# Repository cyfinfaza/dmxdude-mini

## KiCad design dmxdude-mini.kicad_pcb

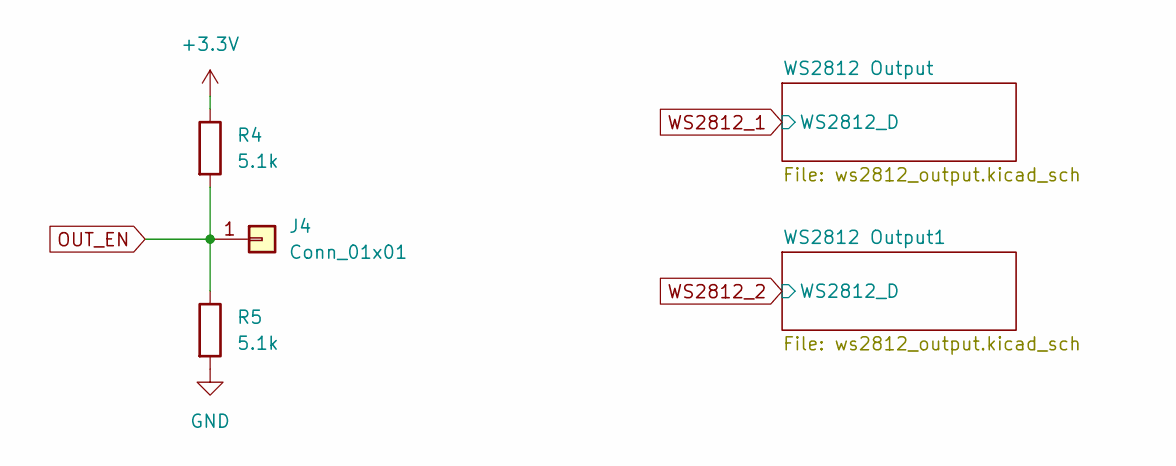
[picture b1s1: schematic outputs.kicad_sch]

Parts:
J4: Conn_01x01; PinHeader_1x01_P2.54mm_Vertical
R4, R5: 5.1k; R_0603_1608Metric_Pad0.98x0.95mm_HandSolder

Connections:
+3.3V: R4.1; also elsewhere on the board
GND: R5.2; also elsewhere on the board
OUT_EN: J4.1, R4.2, R5.1; also elsewhere on the board

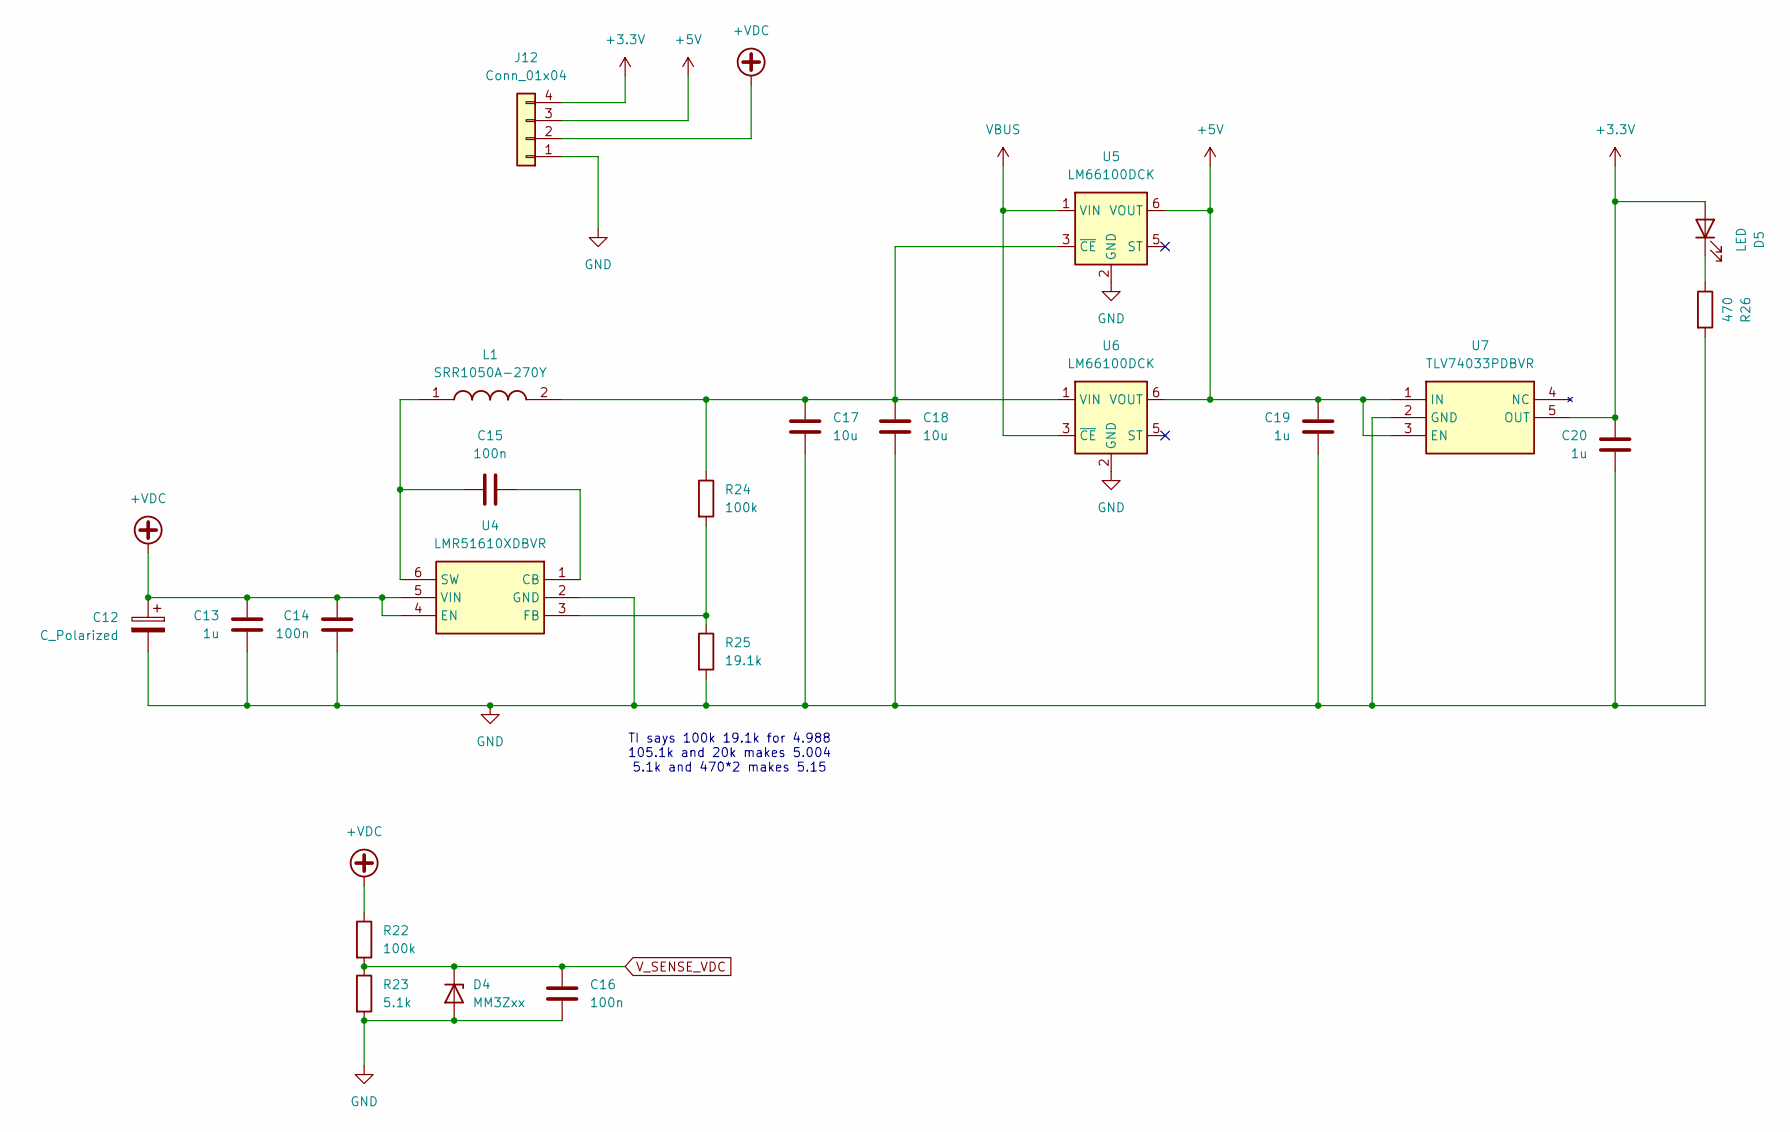
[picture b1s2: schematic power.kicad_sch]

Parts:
C12: C_Polarized; CP_Radial_D5.0mm_P2.00mm
C13, C19, C20: 1u; C_0603_1608Metric_Pad1.08x0.95mm_HandSolder
C14, C15, C16: 100n; C_0603_1608Metric_Pad1.08x0.95mm_HandSolder
C17, C18: 10u; C_0805_2012Metric_Pad1.18x1.45mm_HandSolder
D4: MM3Zxx; D_SOD-323F
D5: LED; LED_0603_1608Metric_Pad1.05x0.95mm_HandSolder
J12: Conn_01x04; PinHeader_1x04_P2.54mm_Vertical
L1: SRR1050A-270Y; SRR1050A221Y; Mouser Part Number 652-SRR1050A-270Y
R22, R24: 100k; R_0603_1608Metric_Pad0.98x0.95mm_HandSolder
R23: 5.1k; R_0603_1608Metric_Pad0.98x0.95mm_HandSolder
R25: 19.1k; R_0603_1608Metric_Pad0.98x0.95mm_HandSolder
R26: 470; R_0603_1608Metric_Pad0.98x0.95mm_HandSolder
U4: LMR51610XDBVR; SOT95P280X145-6N; Mouser Part Number 595-LMR51610XDBVR
U5, U6: LM66100DCK; SOT-363_SC-70-6
U7: TLV74033PDBVR; SOT95P280X145-5N; Mouser Part Number 595-TLV74033PDBVR

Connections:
+3.3V: C20.2, D5.2 (A), J12.4, U7.5 (OUT); also elsewhere on the board
+5V: C19.2, J12.3, U5.6 (VOUT), U6.6 (VOUT), U7.1 (IN), U7.3 (EN); also elsewhere on the board
+VDC: C12.1, C13.2, C14.2, J12.2, R22.1, U4.4 (EN), U4.5 (VIN); also elsewhere on the board
GND: C12.2, C13.1, C14.1, C16.2, C17.2, C18.2, C19.1, C20.1, D4.2 (A), J12.1, R23.2, R25.2, R26.2, U4.2 (GND), U5.2 (GND), U6.2 (GND), U7.2 (GND); also elsewhere on the board
unnamed: D5.1 (K), R26.1
unnamed: C15.2, U4.1 (CB)
unnamed: R24.2, R25.1, U4.3 (FB)
unnamed: C15.1, L1.1, U4.6 (SW)
unnamed: C17.1, C18.1, L1.2, R24.1, U5.3 (~CE), U6.1 (VIN)
VBUS: U5.1 (VIN), U6.3 (~CE); also elsewhere on the board
V_SENSE_VDC: C16.1, D4.1 (K), R22.2, R23.1; also elsewhere on the board

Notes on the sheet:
TI says 100k 19.1k for 4.988 105.1k and 20k makes 5.004 5.1k and 470*2 makes 5.15

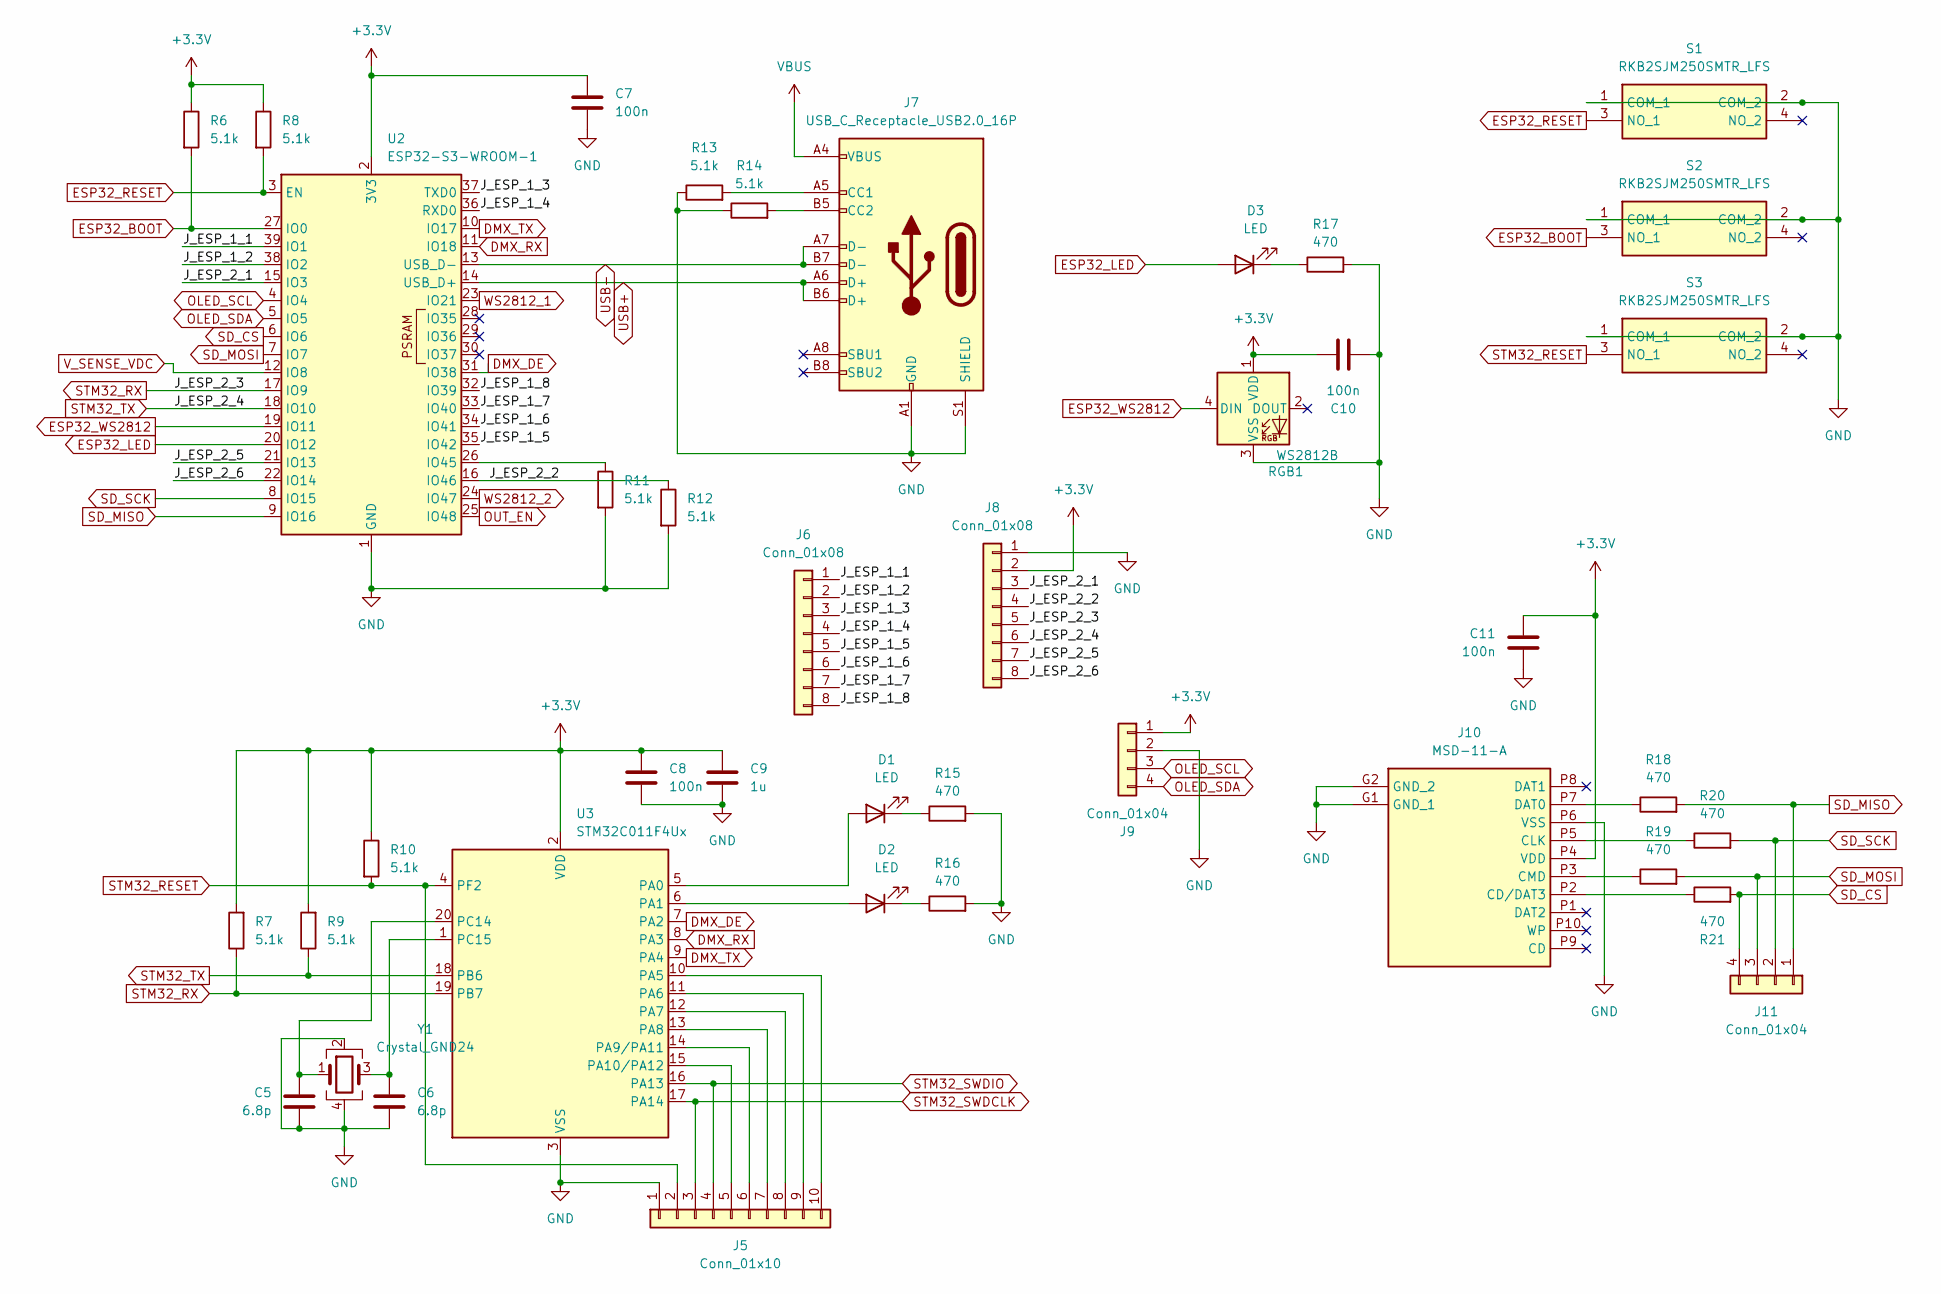
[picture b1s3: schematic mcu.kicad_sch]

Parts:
C5, C6: 6.8p; C_0603_1608Metric_Pad1.08x0.95mm_HandSolder
C7, C8, C10, C11: 100n; C_0603_1608Metric_Pad1.08x0.95mm_HandSolder
C9: 1u; C_0603_1608Metric_Pad1.08x0.95mm_HandSolder
D1, D2, D3: LED; LED_0603_1608Metric_Pad1.05x0.95mm_HandSolder
J5: Conn_01x10; PinHeader_1x10_P2.54mm_Vertical
J6, J8: Conn_01x08; PinHeader_1x08_P2.54mm_Vertical
J7: USB_C_Receptacle_USB2.0_16P; USB_C_Receptacle_HRO_TYPE-C-31-M-12
J9, J11: Conn_01x04; PinHeader_1x04_P2.54mm_Vertical
J10: MSD-11-A; MSD11A; Mouser Part Number 179-MSD-11-A
R6, R7, R8, R9, R10, R11, R12, R13, R14: 5.1k; R_0603_1608Metric_Pad0.98x0.95mm_HandSolder
R15, R16, R17, R18, R19, R20, R21: 470; R_0603_1608Metric_Pad0.98x0.95mm_HandSolder
RGB1: WS2812B; LED_WS2812B_PLCC4_5.0x5.0mm_P3.2mm
S1, S2, S3: RKB2SJM250SMTR_LFS; RKB2SJM250SMTRLFS; Mouser Part Number 611-RKB2SJM250SMTRLF
U2: ESP32-S3-WROOM-1; ESP32-S3-WROOM-2
U3: STM32C011F4Ux; ST_UFQFPN-20_3x3mm_P0.5mm
Y1: Crystal_GND24; Crystal_SMD_Abracon_ABM8AIG-4Pin_3.2x2.5mm

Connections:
+3.3V: C7.1, C8.1, C9.1, C10.1, C11.1, J8.2, J9.1, J10.P4 (VDD), R6.1, R7.2, R8.1, R9.2, R10.1, RGB1.1 (VDD), U2.2 (3V3), U3.2 (VDD); also elsewhere on the board
/MCU/J_ESP_1_1: J6.1, U2.39 (IO1)
/MCU/J_ESP_1_2: J6.2, U2.38 (IO2)
/MCU/J_ESP_1_3: J6.3, U2.37 (TXD0)
/MCU/J_ESP_1_4: J6.4, U2.36 (RXD0)
/MCU/J_ESP_1_5: J6.5, U2.35 (IO42)
/MCU/J_ESP_1_6: J6.6, U2.34 (IO41)
/MCU/J_ESP_1_7: J6.7, U2.33 (IO40)
/MCU/J_ESP_1_8: J6.8, U2.32 (IO39)
/MCU/J_ESP_2_1: J8.3, U2.15 (IO3)
/MCU/J_ESP_2_2: J8.4, R12.1, U2.16 (IO46)
/MCU/J_ESP_2_5: J8.7, U2.21 (IO13)
/MCU/J_ESP_2_6: J8.8, U2.22 (IO14)
DMX_DE: U2.31 (IO38), U3.7 (PA2); also elsewhere on the board
DMX_RX: U2.11 (IO18), U3.8 (PA3); also elsewhere on the board
DMX_TX: U2.10 (IO17), U3.9 (PA4); also elsewhere on the board
ESP32_BOOT: R6.2, S2.3 (NO_1), U2.27 (IO0)
ESP32_LED: D3.2 (A), U2.20 (IO12)
ESP32_RESET: R8.2, S1.3 (NO_1), U2.3 (EN)
ESP32_WS2812: RGB1.4 (DIN), U2.19 (IO11)
GND: C5.2, C6.2, C7.2, C8.2, C9.2, C10.2, C11.2, J5.1, J7.A1 (GND), J7.A12 (GND), J7.B1 (GND), J7.B12 (GND), J7.S1 (SHIELD), J8.1, J9.2, J10.G1 (GND_1), J10.G2 (GND_2), J10.P6 (VSS), R11.2, R12.2, R13.1, R14.1, R15.2, R16.2, R17.2, RGB1.3 (VSS), S1.1 (COM_1), S1.2 (COM_2), S2.1 (COM_1), S2.2 (COM_2), S3.1 (COM_1), S3.2 (COM_2), U2.1 (GND), U2.40 (GND), U2.41 (GND), U3.3 (VSS), Y1.2, Y1.4; also elsewhere on the board
unnamed: D1.2 (A), U3.5 (PA0)
unnamed: D1.1 (K), R15.1
unnamed: D2.2 (A), U3.6 (PA1)
unnamed: D2.1 (K), R16.1
unnamed: D3.1 (K), R17.1
unnamed: J5.5, U3.15 (PA10/PA12)
unnamed: J5.6, U3.14 (PA9/PA11)
unnamed: J5.7, U3.13 (PA8)
unnamed: J5.8, U3.12 (PA7)
unnamed: J5.9, U3.11 (PA6)
unnamed: J5.10, U3.10 (PA5)
unnamed: J7.A5 (CC1), R13.2
unnamed: J7.B5 (CC2), R14.2
unnamed: J10.P2 (CD/DAT3), R21.1
unnamed: J10.P5 (CLK), R20.1
unnamed: J10.P3 (CMD), R19.1
unnamed: J10.P7 (DAT0), R18.1
unnamed: R11.1, U2.26 (IO45)
unnamed: C5.1, U3.20 (PC14), Y1.1
unnamed: C6.1, U3.1 (PC15), Y1.3
OLED_SCL: J9.3, U2.4 (IO4)
OLED_SDA: J9.4, U2.5 (IO5)
OUT_EN: U2.25 (IO48); also elsewhere on the board
SD_CS: J11.4, R21.2, U2.6 (IO6)
SD_MISO: J11.1, R18.2, U2.9 (IO16)
SD_MOSI: J11.3, R19.2, U2.7 (IO7)
SD_SCK: J11.2, R20.2, U2.8 (IO15)
STM32_RESET: J5.2, R10.2, S3.3 (NO_1), U3.4 (PF2)
STM32_RX: J8.5, R7.1, U2.17 (IO9), U3.19 (PB7)
STM32_SWDCLK: J5.3, U3.17 (PA14)
STM32_SWDIO: J5.4, U3.16 (PA13)
STM32_TX: J8.6, R9.1, U2.18 (IO10), U3.18 (PB6)
USB+: J7.A6 (D+), J7.B6 (D+), U2.14 (USB_D+)
USB-: J7.A7 (D-), J7.B7 (D-), U2.13 (USB_D-)
VBUS: J7.A4 (VBUS), J7.A9 (VBUS), J7.B4 (VBUS), J7.B9 (VBUS); also elsewhere on the board
V_SENSE_VDC: U2.12 (IO8); also elsewhere on the board
WS2812_1: U2.23 (IO21); also elsewhere on the board
WS2812_2: U2.24 (IO47); also elsewhere on the board

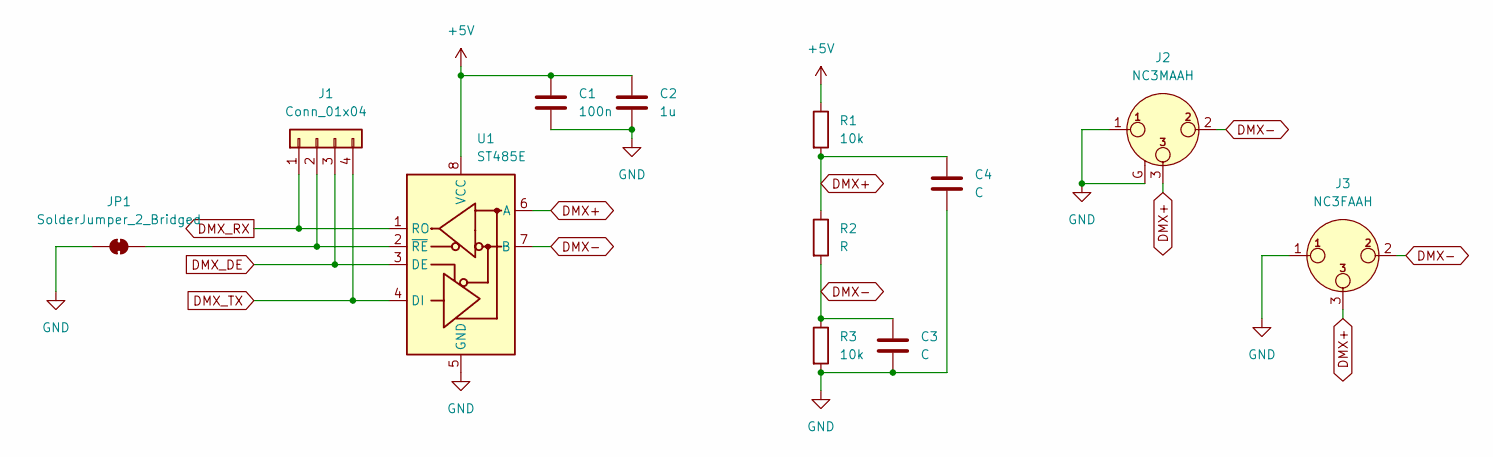
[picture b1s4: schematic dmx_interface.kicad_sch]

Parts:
C1: 100n; C_0603_1608Metric_Pad1.08x0.95mm_HandSolder
C2: 1u; C_0603_1608Metric_Pad1.08x0.95mm_HandSolder
C3, C4: C; C_0603_1608Metric_Pad1.08x0.95mm_HandSolder
J1: Conn_01x04; PinHeader_1x04_P2.54mm_Vertical
J2: NC3MAAH; Jack_XLR_Neutrik_NC3MAAH_Horizontal
J3: NC3FAAH; Jack_XLR_Neutrik_NC3FAAH_Horizontal
JP1: SolderJumper_2_Bridged; SolderJumper-2_P1.3mm_Bridged_RoundedPad1.0x1.5mm
R1, R3: 10k; R_0603_1608Metric_Pad0.98x0.95mm_HandSolder
R2: R; R_0603_1608Metric_Pad0.98x0.95mm_HandSolder
U1: ST485E; SOIC-8_3.9x4.9mm_P1.27mm

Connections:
+5V: C1.1, C2.1, R1.1, U1.8 (VCC); also elsewhere on the board
DMX+: C4.1, J2.3, J3.3, R1.2, R2.1, U1.6 (A)
DMX-: C3.1, J2.2, J3.2, R2.2, R3.1, U1.7 (B)
DMX_DE: J1.3, U1.3 (DE); also elsewhere on the board
DMX_RX: J1.1, U1.1 (RO); also elsewhere on the board
DMX_TX: J1.4, U1.4 (DI); also elsewhere on the board
GND: C1.2, C2.2, C3.2, C4.2, J2.1, J2.G, J3.1, JP1.1 (A), R3.2, U1.5 (GND); also elsewhere on the board
unnamed: J1.2, JP1.2 (B), U1.2 (~RE)

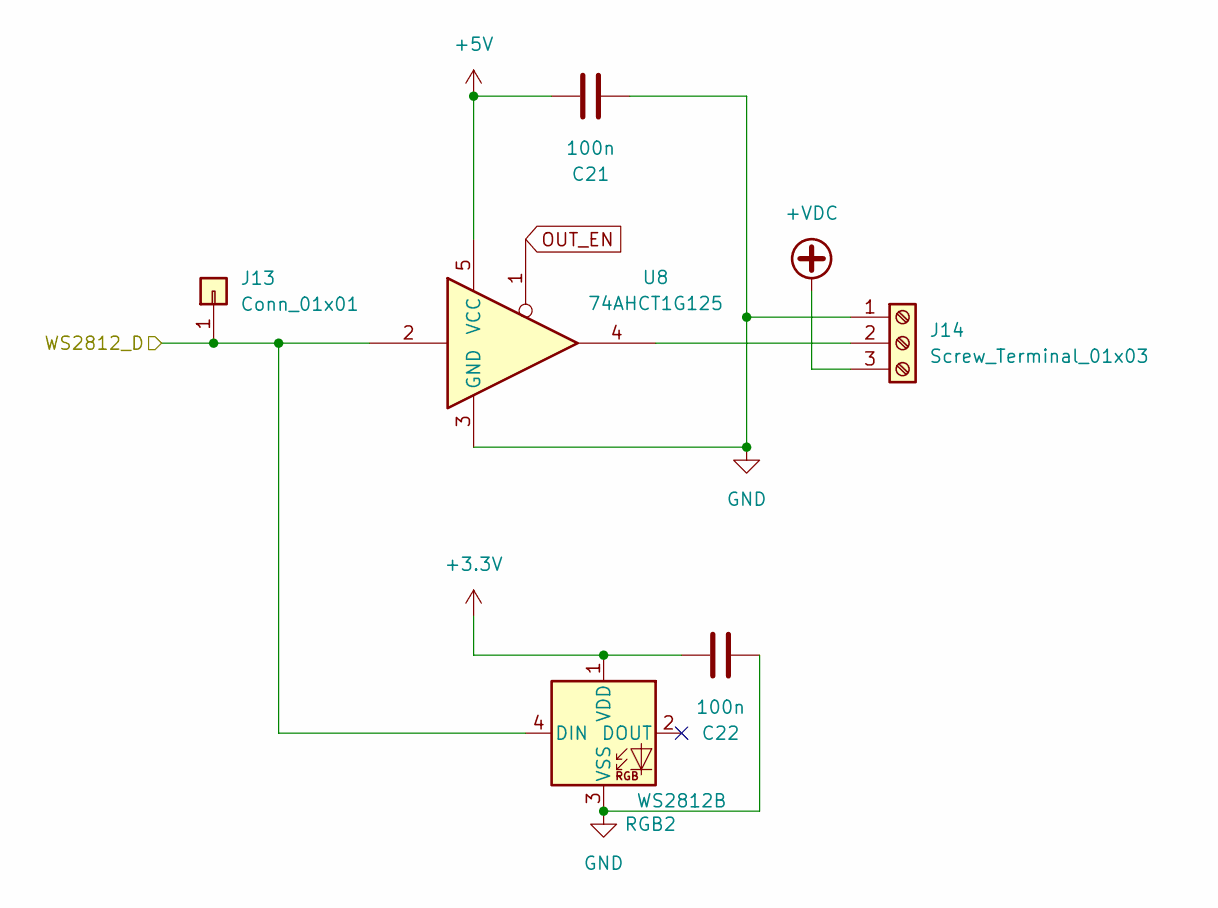
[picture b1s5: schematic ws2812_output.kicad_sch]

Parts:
C21, C22: 100n; C_0603_1608Metric_Pad1.08x0.95mm_HandSolder
J13: Conn_01x01; PinHeader_1x01_P2.54mm_Vertical
J14: Screw_Terminal_01x03; TerminalBlock_MetzConnect_Type101_RT01603HBWC_1x03_P5.08mm_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
RGB2: WS2812B; LED_WS2812B_PLCC4_5.0x5.0mm_P3.2mm
U8: 74AHCT1G125; SOT-353_SC-70-5_Handsoldering

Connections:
+3.3V: C22.1, RGB2.1 (VDD); also elsewhere on the board
+5V: C21.1, U8.5 (VCC); also elsewhere on the board
+VDC: J14.3; also elsewhere on the board
GND: C21.2, C22.2, J14.1, RGB2.3 (VSS), U8.3 (GND); also elsewhere on the board
unnamed: J14.2, U8.4
OUT_EN: U8.1; also elsewhere on the board
WS2812_1: J13.1, RGB2.4 (DIN), U8.2; also elsewhere on the board

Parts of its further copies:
C23, C24: 100n; C_0603_1608Metric_Pad1.08x0.95mm_HandSolder
J15: Conn_01x01; PinHeader_1x01_P2.54mm_Vertical
J16: Screw_Terminal_01x03; TerminalBlock_MetzConnect_Type101_RT01603HBWC_1x03_P5.08mm_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
RGB3: WS2812B; LED_WS2812B_PLCC4_5.0x5.0mm_P3.2mm
U9: 74AHCT1G125; SOT-353_SC-70-5_Handsoldering

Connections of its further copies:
+3.3V: C24.1, RGB3.1 (VDD); also elsewhere on the board
+5V: C23.1, U9.5 (VCC); also elsewhere on the board
+VDC: J16.3; also elsewhere on the board
GND: C23.2, C24.2, J16.1, RGB3.3 (VSS), U9.3 (GND); also elsewhere on the board
unnamed: J16.2, U9.4
OUT_EN: U9.1; also elsewhere on the board
WS2812_2: J15.1, RGB3.4 (DIN), U9.2; also elsewhere on the board

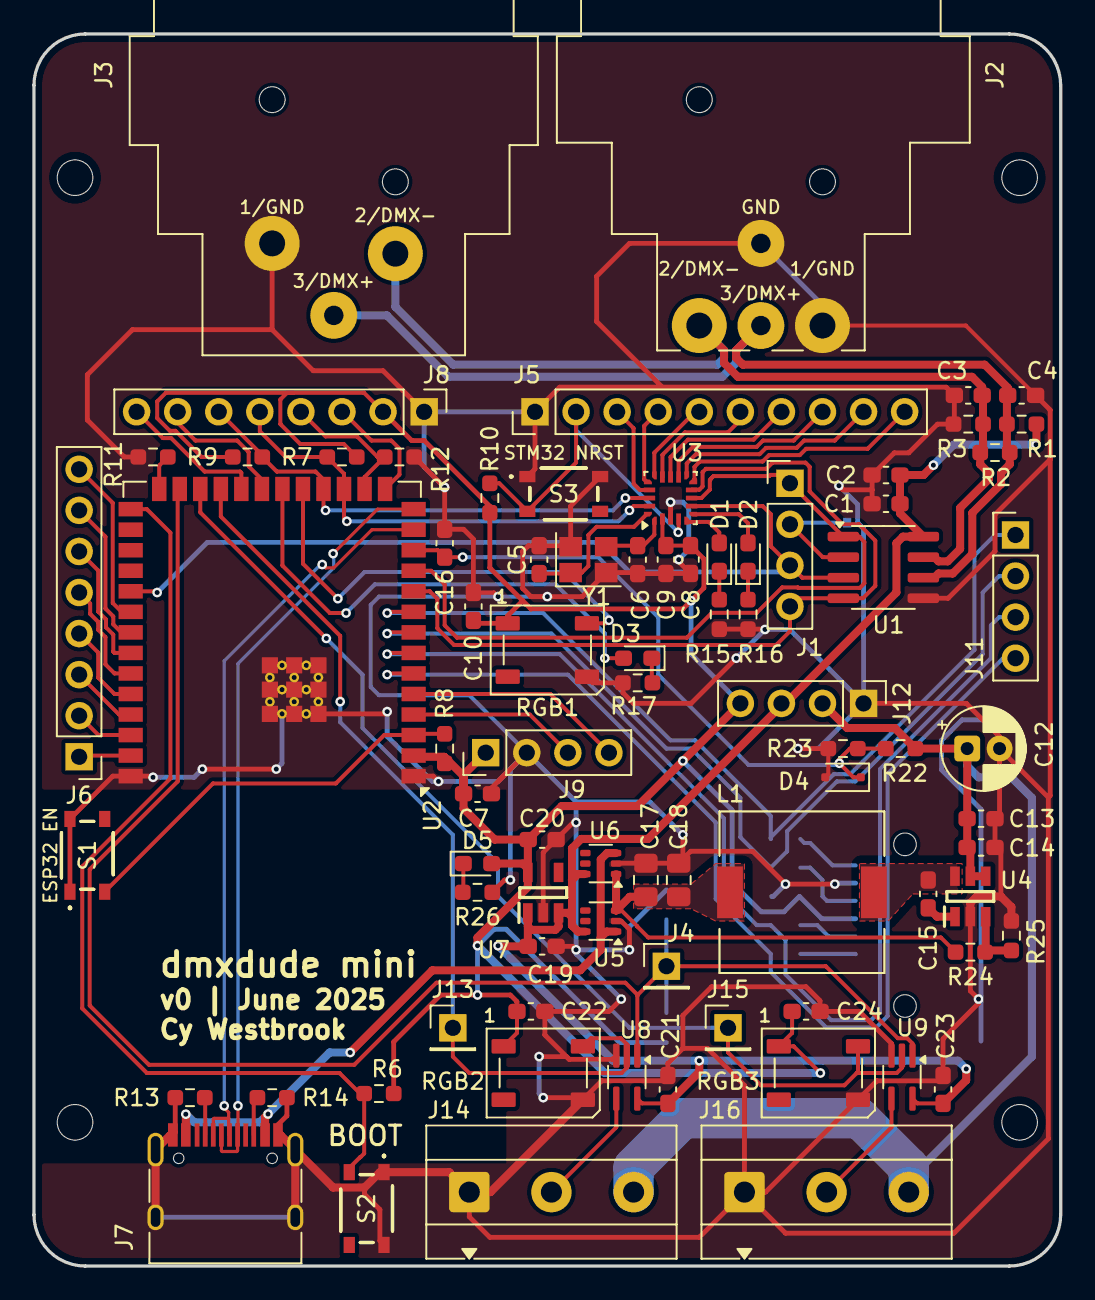
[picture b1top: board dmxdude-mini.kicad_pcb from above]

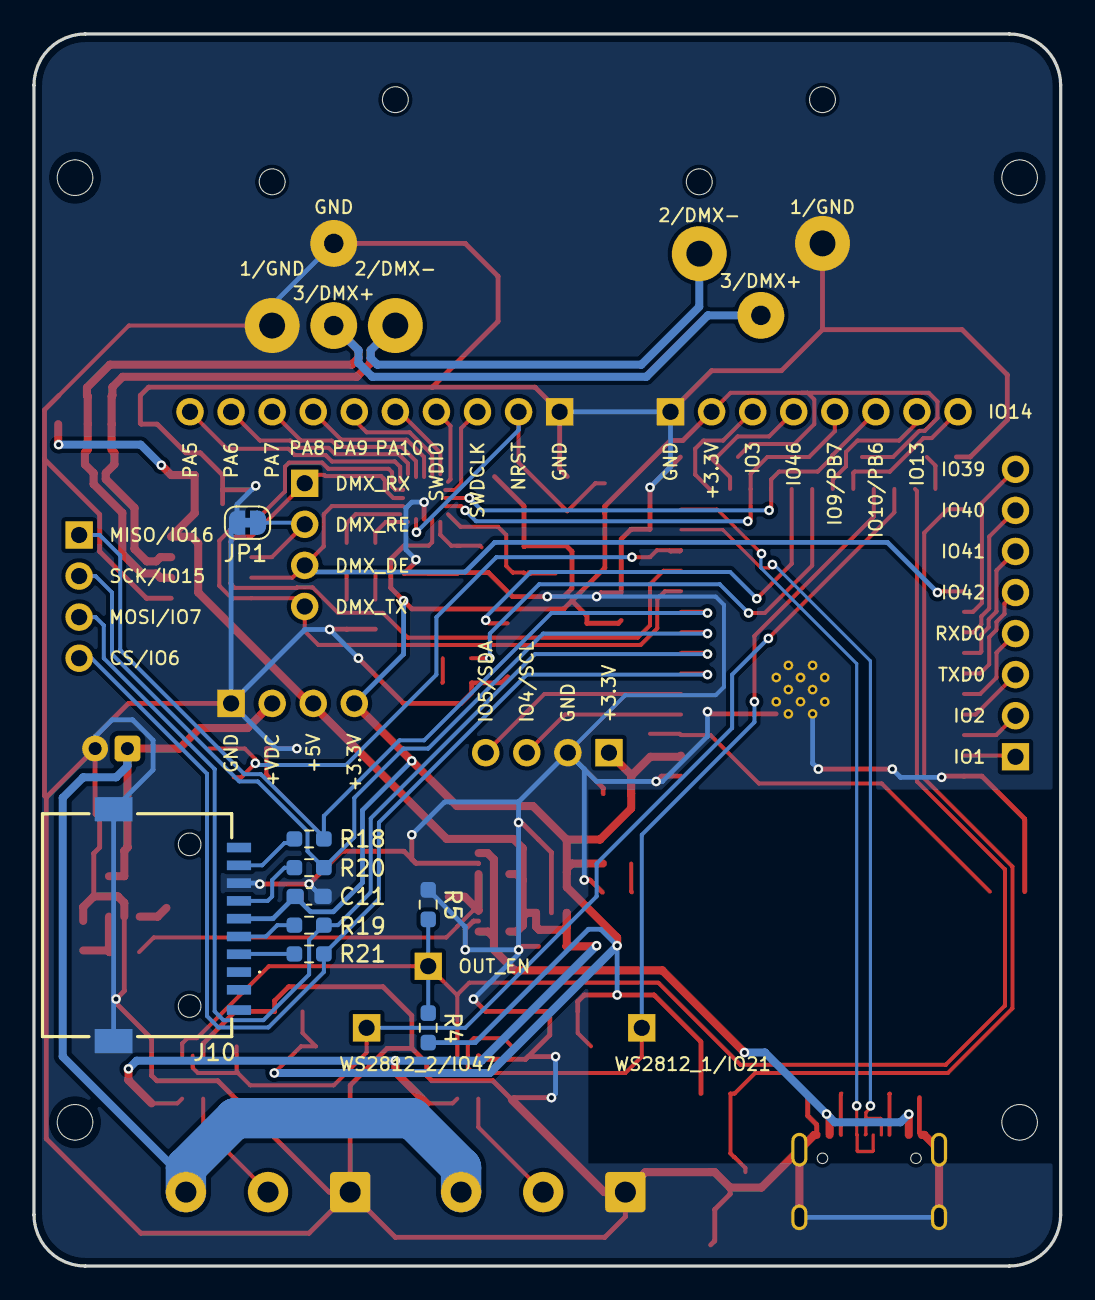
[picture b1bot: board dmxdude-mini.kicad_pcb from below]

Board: 2 copper layers, 63.5 x 76.2 mm, 89 parts (9 on the bottom side), 71 nets.

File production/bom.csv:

Designator,Footprint,Quantity,Value,LCSC Part #
"C1, C10, C11, C14, C15, C16, C21, C22, C23, C24, C7, C8",0603,12,100n,
C12,CP_Radial_D5.0mm_P2.00mm,1,C_Polarized,
"C13, C19, C2, C20, C9",0603,5,1u,
"C17, C18",0805,2,10u,
"C5, C6",0603,2,6.8p,
"D1, D2, D3, D5",0603,4,LED,
D4,D_SOD-323F,1,MM3Zxx,
"J1, J11, J12, J9",PinHeader_1x04_P2.54mm_Vertical,4,Conn_01x04,
J10,MSD11A,1,MSD-11-A,
"J13, J15, J4",PinHeader_1x01_P2.54mm_Vertical,3,Conn_01x01,
"J14, J16",TerminalBlock_MetzConnect_Type101_RT01603HBWC_1x03_P5.08mm_Horizontal,2,Screw_Terminal_01x03,
J2,Jack_XLR_Neutrik_NC3MAAH_Horizontal,1,NC3MAAH,
J3,Jack_XLR_Neutrik_NC3FAAH_Horizontal,1,NC3FAAH,
J5,PinHeader_1x10_P2.54mm_Vertical,1,Conn_01x10,
"J6, J8",PinHeader_1x08_P2.54mm_Vertical,2,Conn_01x08,
J7,USB_C_Receptacle_HRO_TYPE-C-31-M-12,1,USB_C_Receptacle_USB2.0_16P,
L1,SRR1050A221Y,1,SRR1050A-270Y,
"R1, R3",0603,2,10k,
"R10, R11, R12, R13, R14, R23, R4, R5, R6, R7, R8, R9",0603,12,5.1k,
"R15, R16, R17, R18, R19, R20, R21, R26",0603,8,470,
"R22, R24",0603,2,100k,
R25,0603,1,19.1k,
"RGB1, RGB2, RGB3",LED_WS2812B_PLCC4_5.0x5.0mm_P3.2mm,3,WS2812B,
"S1, S2, S3",RKB2SJM250SMTRLFS,3,RKB2SJM250SMTR_LFS,
U1,SOIC-8_3.9x4.9mm_P1.27mm,1,ST485E,
U2,ESP32-S3-WROOM-2,1,ESP32-S3-WROOM-1,
U3,ST_UFQFPN-20_3x3mm_P0.5mm,1,STM32C011F4Ux,
U4,SOT95P280X145-6N,1,LMR51610XDBVR,
"U5, U6",SOT-363_SC-70-6,2,LM66100DCK,
U7,SOT95P280X145-5N,1,TLV74033PDBVR,
"U8, U9",SOT-353_SC-70-5_Handsoldering,2,74AHCT1G125,
Y1,Crystal_SMD_Abracon_ABM8AIG-4Pin_3.2x2.5mm,1,Crystal_GND24,

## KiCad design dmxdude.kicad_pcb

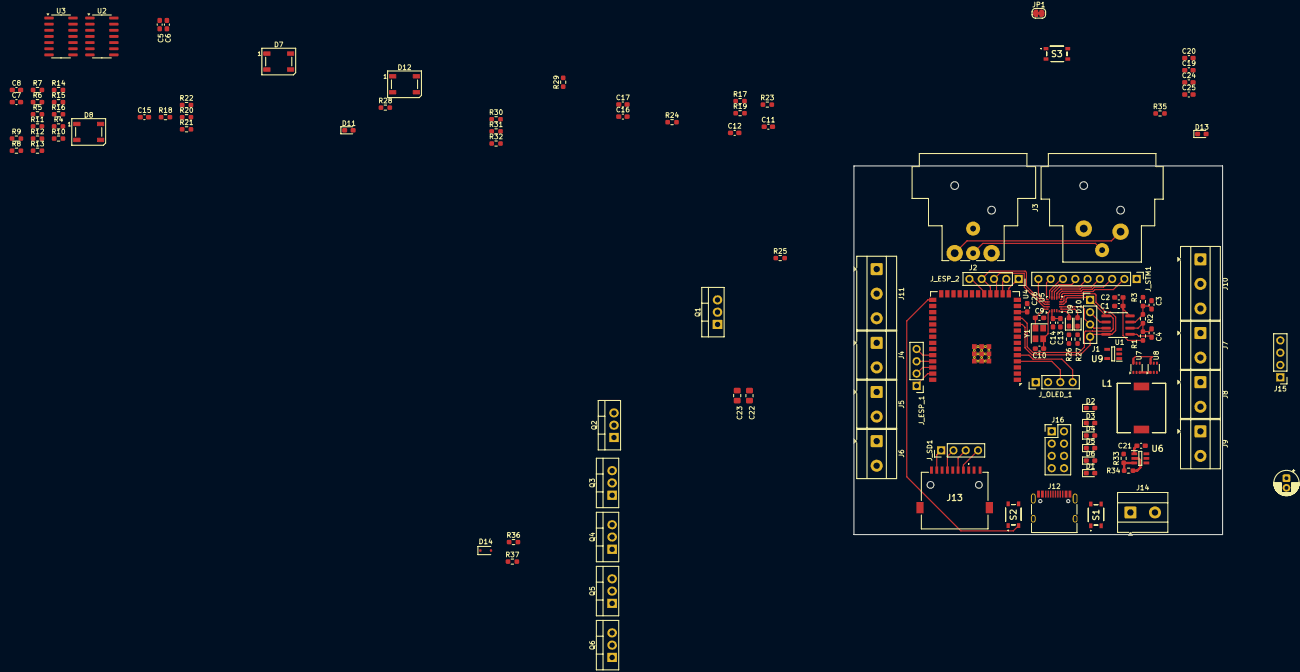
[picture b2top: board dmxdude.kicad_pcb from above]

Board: 2 copper layers, 76.2 x 76.2 mm, 119 parts (0 on the bottom side), 85 nets.

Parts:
C1, C5, C6, C7, C8, C11, C13, C15, C17, C20, C21, C26: 100n; C_0603_1608Metric_Pad1.08x0.95mm_HandSolder
C2, C12, C14, C16, C19, C24, C25: 1u; C_0603_1608Metric_Pad1.08x0.95mm_HandSolder
C3, C4: C; C_0603_1608Metric_Pad1.08x0.95mm_HandSolder
C9, C10: 6.8p; C_0603_1608Metric_Pad1.08x0.95mm_HandSolder
C18: C_Polarized; CP_Radial_D5.0mm_P2.00mm
C22, C23: 10u; C_0805_2012Metric_Pad1.18x1.45mm_HandSolder
D1, D2, D3, D4, D5, D6, D9, D10, D11, D13: LED; LED_0603_1608Metric_Pad1.05x0.95mm_HandSolder
D7, D8, D12: WS2812B; LED_WS2812B_PLCC4_5.0x5.0mm_P3.2mm
D14: MM3Zxx; D_SOD-323F
J1, J15: Conn_01x04; PinHeader_1x04_P2.54mm_Vertical
J2: NC3MAAH; Jack_XLR_Neutrik_NC3MAAH_Horizontal
J3: NC3FAAH; Jack_XLR_Neutrik_NC3FAAH_Horizontal
J4, J5, J6, J7, J8, J9, J14: Screw_Terminal_01x02; TerminalBlock_MetzConnect_Type101_RT01602HBWC_1x02_P5.08mm_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
J10, J11: Screw_Terminal_01x03; TerminalBlock_MetzConnect_Type101_RT01603HBWC_1x03_P5.08mm_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
J12: USB_C_Receptacle_USB2.0_16P; USB_C_Receptacle_HRO_TYPE-C-31-M-12
J13: MSD-11-A; MSD11A
J16: Conn_02x04_Top_Bottom; PinHeader_2x04_P2.54mm_Vertical
JP1: SolderJumper_2_Bridged; SolderJumper-2_P1.3mm_Bridged_RoundedPad1.0x1.5mm
J_ESP_1: Conn_01x04; PinHeader_1x04_P2.54mm_Vertical
J_ESP_2: Conn_01x05; PinSocket_1x05_P2.54mm_Vertical
J_OLED_1: Conn_01x04; PinHeader_1x04_P2.54mm_Vertical
J_SD1: Conn_01x04; PinHeader_1x04_P2.54mm_Vertical
J_STM1: Conn_01x09; PinHeader_1x09_P2.54mm_Vertical
L1: SRR1050A-270Y; SRR1050A221Y
Q1, Q2, Q3, Q4, Q5, Q6: IRLZ44N; TO-220-3_Vertical
R1, R3, R5, R6, R7, R8, R9, R10, R29, R30, R31, R32: 10k; R_0603_1608Metric_Pad0.98x0.95mm_HandSolder
R2: R; R_0603_1608Metric_Pad0.98x0.95mm_HandSolder
R4, R17, R18, R19, R20, R21, R22, R23, R24, R25, R37: 5.1k; R_0603_1608Metric_Pad0.98x0.95mm_HandSolder
R11, R12, R13, R14, R15, R16, R26, R27, R28, R35: 470; R_0603_1608Metric_Pad0.98x0.95mm_HandSolder
R33, R36: 100k; R_0603_1608Metric_Pad0.98x0.95mm_HandSolder
R34: 19.1k; R_0603_1608Metric_Pad0.98x0.95mm_HandSolder
S1, S2, S3: RKB2SJM250SMTR_LFS; RKB2SJM250SMTRLFS
U1: ST485E; SOIC-8_3.9x4.9mm_P1.27mm
U2, U3: 74AHCT125; SOIC-14_3.9x8.7mm_P1.27mm
U4: ESP32-S3-WROOM-1; ESP32-S3-WROOM-2
U5: STM32C011F4Ux; ST_UFQFPN-20_3x3mm_P0.5mm
U6: LMR51610XDBVR; SOT95P280X145-6N
U7, U8: LM66100DCK; SOT-363_SC-70-6
U9: TLV74033PDBVR; SOT95P280X145-5N
Y1: Crystal_GND24; Crystal_SMD_Abracon_ABM8AIG-4Pin_3.2x2.5mm

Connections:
+3.3V: C7.1, C8.1, C11.1, C12.1, C13.1, C14.1, C15.1, C16.1, C17.1, C25.2, D7.1 (VDD), D8.1 (VDD), D12.1 (VDD), D13.2 (A), J13.P4 (VDD), J15.2, J_OLED_1.1, R4.1, R17.1, R18.2, R19.1, R20.2, R21.1, R29.1, R30.1, R31.1, R32.1, U4.2 (3V3), U5.2 (VDD), U9.5 (OUT)
+5V: C1.1, C2.1, C5.2, C6.2, C24.2, J15.3, R1.1, U1.8 (VCC), U2.14 (VCC), U3.14 (VCC), U7.6 (VOUT), U8.6 (VOUT), U9.1 (IN), U9.3 (EN)
+VDC: C18.1, C19.2, C20.2, J4.2, J5.2, J6.2, J7.2, J8.2, J9.2, J10.3, J11.3, J14.2, J15.4, R36.1, U6.4 (EN), U6.5 (VIN)
/MCU/J_ESP_1_1: J_ESP_1.1, U4.39 (IO1)
/MCU/J_ESP_1_2: J_ESP_1.2, U4.38 (IO2)
/MCU/J_ESP_1_3: J_ESP_1.3, U4.37 (TXD0)
/MCU/J_ESP_1_4: J_ESP_1.4, U4.36 (RXD0)
/MCU/J_ESP_2_1: J_ESP_2.1, U4.15 (IO3)
/MCU/J_ESP_2_2: J_ESP_2.2, R23.1, U4.16 (IO46)
/MCU/J_ESP_2_5: J_ESP_2.5, U4.19 (IO11)
DMX+: C4.1, J2.3, J3.3, R1.2, R2.1, U1.6 (A)
DMX-: C3.1, J2.2, J3.2, R2.2, R3.1, U1.7 (B)
DMX_DE: J1.3, U1.3 (DE), U4.31 (IO38), U5.7 (PA2)
DMX_RX: J1.1, U1.1 (RO), U4.11 (IO18), U5.8 (PA3)
DMX_TX: J1.4, U1.4 (DI), U4.10 (IO17), U5.9 (PA4)
ESP32_BOOT: R17.2, S2.3 (NO_1), U4.27 (IO0)
ESP32_LED: D11.2 (A), D12.4 (DIN), U4.20 (IO12)
ESP32_RESET: R19.2, S1.3 (NO_1), U4.3 (EN)
GND: C1.2, C2.2, C3.2, C4.2, C5.1, C6.1, C7.2, C8.2, C9.2, C10.2, C11.2, C12.2, C13.2, C14.2, C15.2, C16.2, C17.2, C18.2, C19.1, C20.1, C22.2, C23.2, C24.1, C25.1, C26.2, D7.3 (VSS), D8.3 (VSS), D12.3 (VSS), D14.2 (A), J2.1, J2.G, J3.1, J10.1, J11.1, J12.A1 (GND), J12.A12 (GND), J12.B1 (GND), J12.B12 (GND), J12.S1 (SHIELD), J13.G1 (GND_1), J13.G2 (GND_2), J13.P6 (VSS), J14.1, J15.1, JP1.1 (A), J_OLED_1.2, J_STM1.1, Q1.3 (S), Q2.3 (S), Q3.3 (S), Q4.3 (S), Q5.3 (S), Q6.3 (S), R3.2, R5.2, R6.2, R7.2, R8.2, R9.2, R10.2, R11.2, R12.2, R13.2, R14.2, R15.2, R16.2, R22.2, R23.2, R24.1, R25.1, R26.2, R27.2, R28.2, R34.2, R35.2, R37.2, S1.1 (COM_1), S1.2 (COM_2), S2.1 (COM_1), S2.2 (COM_2), S3.1 (COM_1), S3.2 (COM_2), U1.5 (GND), U2.7 (GND), U3.7 (GND), U4.1 (GND), U4.40 (GND), U4.41 (GND), U5.3 (VSS), U6.2 (GND), U7.2 (GND), U8.2 (GND), U9.2 (GND), Y1.2, Y1.4
unnamed: D1.1 (K), R11.1
unnamed: D2.1 (K), R12.1
unnamed: D3.1 (K), R13.1
unnamed: D4.1 (K), R14.1
unnamed: D5.1 (K), R15.1
unnamed: D6.1 (K), R16.1
unnamed: D9.2 (A), U5.5 (PA0)
unnamed: D9.1 (K), R26.1
unnamed: D10.2 (A), U5.6 (PA1)
unnamed: D10.1 (K), R27.1
unnamed: D11.1 (K), R28.1
unnamed: D13.1 (K), R35.1
unnamed: J1.2, JP1.2 (B), U1.2 (~RE)
unnamed: J4.1, Q1.2 (D)
unnamed: J5.1, Q2.2 (D)
unnamed: J6.1, Q3.2 (D)
unnamed: J7.1, Q4.2 (D)
unnamed: J8.1, Q5.2 (D)
unnamed: J9.1, Q6.2 (D)
unnamed: J10.2, U3.3
unnamed: J11.2, U3.6
unnamed: J12.A5 (CC1), R24.2
unnamed: J12.B5 (CC2), R25.2
unnamed: J_STM1.2, U5.10 (PA5)
unnamed: J_STM1.3, U5.11 (PA6)
unnamed: J_STM1.4, U5.12 (PA7)
unnamed: J_STM1.5, U5.13 (PA8)
unnamed: J_STM1.6, U5.14 (PA9/PA11)
unnamed: J_STM1.7, U5.15 (PA10/PA12)
unnamed: Q1.1 (G), R5.1, U3.8
unnamed: Q2.1 (G), R6.1, U3.11
unnamed: Q3.1 (G), R7.1, U2.3
unnamed: Q4.1 (G), R8.1, U2.6
unnamed: Q5.1 (G), R9.1, U2.8
unnamed: Q6.1 (G), R10.1, U2.11
unnamed: R22.1, U4.26 (IO45)
unnamed: C9.1, U5.20 (PC14), Y1.1
unnamed: C10.1, U5.1 (PC15), Y1.3
unnamed: C21.2, U6.1 (CB)
unnamed: R33.2, R34.1, U6.3 (FB)
unnamed: C21.1, L1.1, U6.6 (SW)
unnamed: C22.1, C23.1, L1.2, R33.1, U7.3 (~CE), U8.1 (VIN)
OLED_SCL: J_OLED_1.3, U4.4 (IO4)
OLED_SDA: J_OLED_1.4, U4.5 (IO5)
OUT_EN: R4.2, U2.1, U2.4, U2.10, U2.13, U3.1, U3.4, U3.10, U3.13, U4.25 (IO48)
SD_CS: J13.P2 (CD/DAT3), J_SD1.4, R29.2, U4.6 (IO6)
SD_MISO: J13.P7 (DAT0), J_SD1.1, R32.2, U4.8 (IO15)
SD_MOSI: J13.P3 (CMD), J_SD1.3, R30.2, U4.7 (IO7)
SD_SCK: J13.P5 (CLK), J_SD1.2, R31.2, U4.9 (IO16)
STM32_RESET: R21.2, S3.3 (NO_1), U5.4 (PF2)
STM32_RX: J_ESP_2.3, R18.1, U4.17 (IO9), U5.19 (PB7)
STM32_SWDCLK: J_STM1.9, U5.17 (PA14)
STM32_SWDIO: J_STM1.8, U5.16 (PA13)
STM32_TX: J_ESP_2.4, R20.1, U4.18 (IO10), U5.18 (PB6)
SW_G_1: D1.2 (A), J16.1, U3.9, U4.21 (IO13)
SW_G_2: D2.2 (A), J16.2, U3.12, U4.22 (IO14)
SW_G_3: D3.2 (A), J16.3, U2.2, U4.32 (IO39)
SW_G_4: D4.2 (A), J16.4, U2.5, U4.33 (IO40)
SW_G_5: D5.2 (A), J16.7, U2.9, U4.34 (IO41)
SW_G_6: D6.2 (A), J16.8, U2.12, U4.35 (IO42)
USB+: J12.A6 (D+), J12.B6 (D+), U4.14 (USB_D+)
USB-: J12.A7 (D-), J12.B7 (D-), U4.13 (USB_D-)
VBUS: J12.A4 (VBUS), J12.A9 (VBUS), J12.B4 (VBUS), J12.B9 (VBUS), U7.1 (VIN), U8.3 (~CE)
V_SENSE_VDC: C26.1, D14.1 (K), R36.2, R37.1, U4.12 (IO8)
WS2812_1: D7.4 (DIN), D8.4 (DIN), J16.5, U3.2, U4.23 (IO21)
WS2812_2: J16.6, U3.5, U4.24 (IO47)

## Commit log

2025-06-17 mcu pinouts and extras
2025-06-19 power circuitry
2025-06-20 add probe headers
2025-06-21 partial layout
2025-06-22 schematic changes for mini
2025-06-22 complete top layer layout
2025-06-23 complete layout, routing, and silkscreen
2025-06-28 final for order 23 june 2025
